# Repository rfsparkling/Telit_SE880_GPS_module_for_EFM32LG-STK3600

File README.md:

This is my evaluation board for interfacing Telit SE880 GPS chip module with EFM32LG-STK3600 EFM32 Leopard Gecko Starter Kit.

I had lot of trouble during the SE880 chip module manufacturing, forget hot air blower! This is a 3D chip module with embedded parts, like capacitors, resistors, etc.
You need to follow the exact heat profile provided by Telit in tha datasheet. So using an SMT heat oven is highly recommended! 

My PCB is assembled (by professional contract manufacturer) and I confirm: it works! The parts are correct.

I have assambled PCBs to sell, please contact me about the details!

Validated Eagle Parts in this project:
Telit SE880
http://www.telit.com/products/product-service-selector/product-service-selector/show/product/jupiter-se880/

EFM32LG-STK3600 interface connector, pinhead connector
https://www.silabs.com/products/mcu/lowpower/Pages/efm32lg-stk3600.aspx

TI TXS0108E 
8-Bit Bidirectional Voltage-Level Shifter For Open-Drain And Push-Pull Application
http://www.ti.com/product/txs0108e

TI LP5907
250mA, Ultra-Low Noise Low-Dropout Regulator
http://www.ti.com/product/LP5907

AVX / Kyocera
TCXO Oscillators 16.369MHz 1.8Volts 2.5mmx2mm Sine Wave
http://www.mouser.co.uk/Search/Refine.aspx?Keyword=581-KT2520F16ACW18T

Abracon 
ABS06-32.768KHZ-T XTAL
http://www.digikey.com/product-detail/en/ABS06-32.768KHZ-T/535-10104-1-ND/2089921

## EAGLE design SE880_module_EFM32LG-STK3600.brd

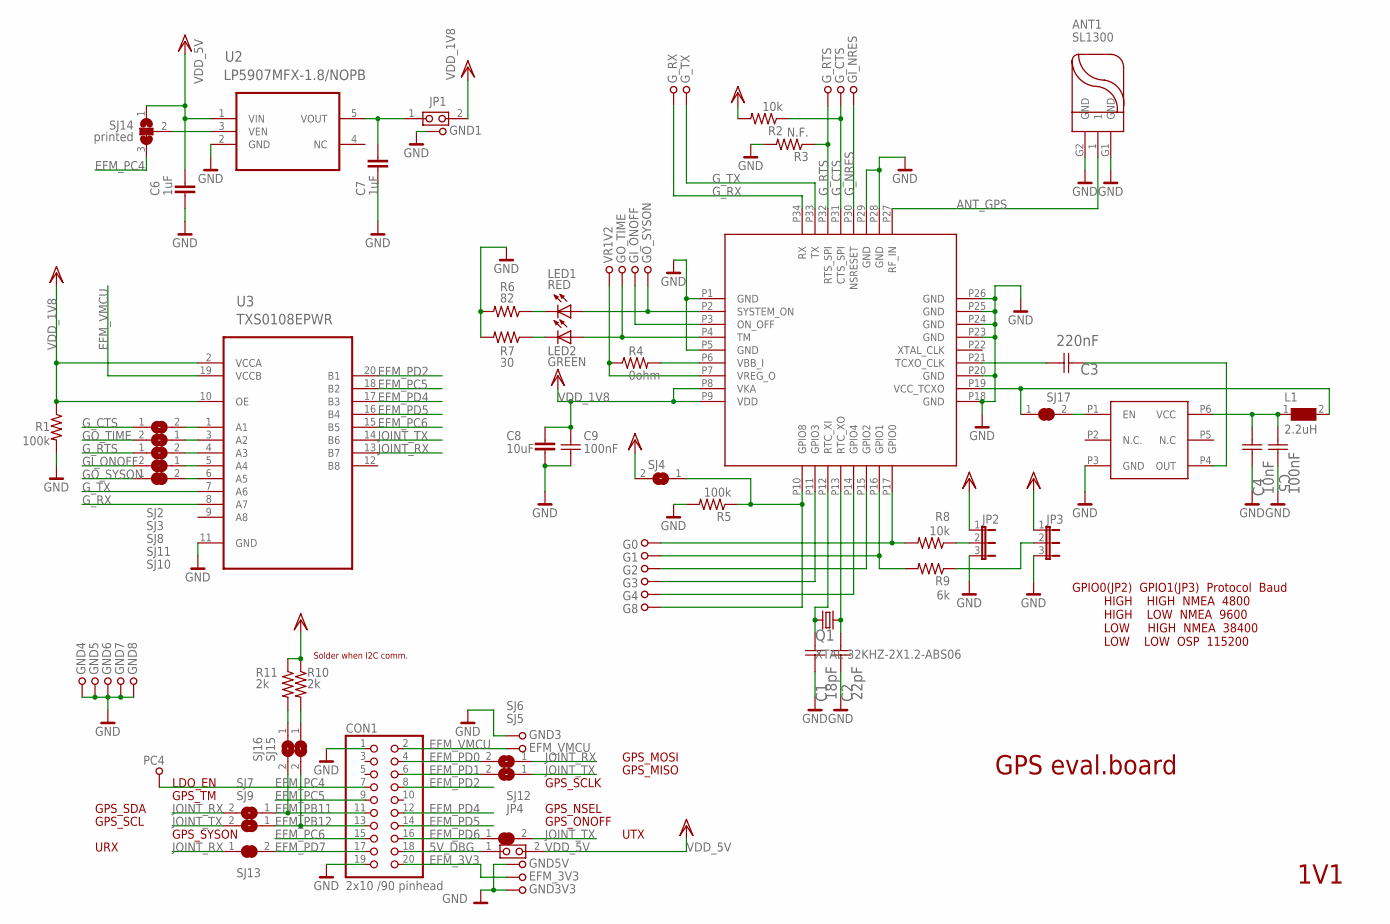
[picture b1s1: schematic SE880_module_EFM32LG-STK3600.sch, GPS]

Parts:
ANT1: SL1300
C1: 18pF; CAPC1005X60N
C2: 22pF; CAPC1005X60N
C3: 220nF; CAPC1005X60N
C4: 10nF; CAPC1005X60N
C5, C9: 100nF; CAPC1005X60N
C6, C7: 1uF; 0603
C8: 10uF; 0603
CON1: 2x10 /90 pinhead; 2X10/90_FEMALE_EFM_MUTANT
EFM_3V3: TESTPOINT39MIL; TESTPOINT1,0
EFM_VMCU: TESTPOINT39MIL; TESTPOINT1,0
G0, G1, G2, G3, G4, G8: TESTPOINT39MIL; TESTPOINT1,0
GI_NRES: TESTPOINT39MIL; TESTPOINT1,0
GI_ONOFF: TESTPOINT39MIL; TESTPOINT1,0
GND1, GND3, GND3V3, GND4, GND5, GND5V, GND6, GND7, GND8: TESTPOINT39MIL; TESTPOINT1,0
GO_SYSON: TESTPOINT39MIL; TESTPOINT1,0
GO_TIME: TESTPOINT39MIL; TESTPOINT1,0
G_CTS: TESTPOINT39MIL; TESTPOINT1,0
G_RTS: TESTPOINT39MIL; TESTPOINT1,0
G_RX: TESTPOINT39MIL; TESTPOINT1,0
G_TX: TESTPOINT39MIL; TESTPOINT1,0
JP1, JP4: JUMPER2-A; PIN2-1R
JP2, JP3: jumper 2mm; JP2
L1: 2.2uH; WE-KI_1008_B
LED1: RED; LED-0603
LED2: GREEN; LED-0603
PC4: TESTPOINT39MIL; TESTPOINT1,0
Q1: XTAL-32KHZ-2X1.2-ABS06; CRYSTAL-SMD-2X1.2-ABS06
Q3: KT2520F16369ACW18TAN; TCXO_2.5X2MM
R1, R5: 100k; R0402
R2, R8: 10k; R0402
R3: N.F.; R0402
R4: 0ohm; 0603-RES
R6: 82; R0402
R7: 30; R0402
R9: 6k; R0402
R10, R11: 2k; R0402
SJ2, SJ3, SJ4, SJ5, SJ6, SJ7, SJ8, SJ9, SJ15, SJ16: printed; JUMPER_SMD_SJ
SJ10, SJ11, SJ12, SJ13, SJ17: printed; JUMPER_SMD_SJ_1
SJ14: printed; JUMPER_SMD_SJ2A
U1: Telit SE880 GPS receiver; LGA-34
U2: LP5907MFX-1.8/NOPB; SOT-23/5-NEW
U3: TXS0108EPWR; SOP65P640X120-20N
VR1V2: TESTPOINT39MIL; TESTPOINT1,0

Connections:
5V_DBG: CON1.18, JP4.1 (A)
ANT_GPS: ANT1.1, U1.P27 (RF_IN)
EFM_3V3: CON1.20, EFM_3V3.1
EFM_PB11: CON1.11, SJ7.1, SJ16.2
EFM_PB12: CON1.13, SJ9.1, SJ15.2
EFM_PC4: CON1.7, PC4.1, SJ14.3
EFM_PC5: CON1.9, U3.18 (B2)
EFM_PC6: CON1.15, U3.15 (B5)
EFM_PD0: CON1.4, SJ6.2
EFM_PD1: CON1.6, SJ5.2
EFM_PD2: CON1.8, U3.20 (B1)
EFM_PD4: CON1.12, U3.17 (B3)
EFM_PD5: CON1.14, U3.16 (B4)
EFM_PD6: CON1.16, SJ12.1
EFM_PD7: CON1.17, SJ13.2
EFM_VMCU: CON1.2, EFM_VMCU.1, U3.19 (VCCB)
GI_ONOFF: GI_ONOFF.1, SJ11.2, U1.P3 (ON_OFF)
GND: ANT1.G1 (GND), ANT1.G2 (GND), C1.2 (C2), C2.2 (C2), C4.2 (C2), C5.2 (C2), C6.1, C7.1, C8.1, C9.2 (C2), CON1.1, CON1.19, GND1.1, GND3.1, GND3V3.1, GND4.1, GND5.1, GND5V.1, GND6.1, GND7.1, GND8.1, JP2.3, JP3.3, Q3.P3 (GND), R1.2, R3.2, R5.2, R6.2, R7.2, U1.P1 (GND), U1.P5 (GND), U1.P18 (GND), U1.P20 (GND), U1.P23 (GND), U1.P24 (GND), U1.P25 (GND), U1.P26 (GND), U1.P28 (GND), U1.P29 (GND), U2.2 (GND), U3.11 (GND)
GO_SYSON: GO_SYSON.1, LED1.A, SJ10.1, U1.P2 (SYSTEM_ON)
GO_TIME: GO_TIME.1, LED2.A, SJ3.2, U1.P4 (TM)
G_CTS: G_CTS.1, R2.1, SJ2.1, U1.P31 (CTS_SPI)
G_NRES: GI_NRES.1, U1.P30 (NSRESET)
G_RTS: G_RTS.1, R3.1, SJ8.1, U1.P32 (RTS_SPI)
G_RX: G_RX.1, U1.P34 (RX), U3.8 (A7)
G_TX: G_TX.1, U1.P33 (TX), U3.7 (A6)
JOINT_RX: SJ6.1, SJ7.2, SJ13.1, U3.13 (B7)
JOINT_TX: SJ5.1, SJ9.2, SJ12.2, U3.14 (B6)
unnamed: C2.1 (C1), Q1.P$2 (2), U1.P13 (RTC_XO)
unnamed: C1.1 (C1), Q1.P$1 (1), U1.P12 (RTC_XI)
unnamed: C3.1 (C1), U1.P21 (TCXO_CLK)
unnamed: C3.2 (C2), Q3.P4 (OUT)
unnamed: C4.1 (C1), C5.1 (C1), L1.1, Q3.P6 (VCC)
unnamed: L1.2, SJ17.1, U1.P19 (VCC_TCXO)
unnamed: G3.1, U1.P11 (GPIO3)
unnamed: C7.2, JP1.1 (A), U2.5 (VOUT)
unnamed: G4.1, U1.P14 (GPIO4)
unnamed: G2.1, U1.P15 (GPIO2)
unnamed: G1.1, R9.2, U1.P16 (GPIO1)
unnamed: G0.1, R8.2, U1.P17 (GPIO0)
unnamed: SJ14.2, U2.3 (VEN)
unnamed: Q3.P1 (EN), SJ17.2
unnamed: R10.2, SJ15.1
unnamed: LED1.C, R6.1
unnamed: R11.2, SJ16.1
unnamed: SJ2.2, U3.1 (A1)
unnamed: R4.2, U1.P6 (VBB_I)
unnamed: R4.1, U1.P7 (VREG_O), VR1V2.1
unnamed: G8.1, R5.1, SJ4.1, U1.P10 (GPIO8)
unnamed: LED2.C, R7.1
unnamed: JP2.2, R8.1
unnamed: JP3.2, R9.1
unnamed: SJ3.1, U3.3 (A2)
unnamed: SJ8.2, U3.4 (A3)
unnamed: SJ11.1, U3.5 (A4)
unnamed: SJ10.2, U3.6 (A5)
VDD_1V8: C8.2, C9.1 (C1), JP1.2 (B), JP2.1, JP3.1, R1.1, R2.2, R10.1, R11.1, SJ4.2, U1.P8 (VKA), U1.P9 (VDD), U3.2 (VCCA), U3.10 (OE)
VDD_5V: C6.2, JP4.2 (B), SJ14.1, U2.1 (VIN)

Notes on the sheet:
GPS eval.board
1V1
GPIO0(JP2) GPIO1(JP3) Protocol Baud HIGH HIGH NMEA 4800 HIGH LOW NMEA 9600 LOW HIGH NMEA 38400 LOW LOW OSP 115200
Solder when I2C comm.
GPS_NSEL
GPS_ONOFF
GPS_SCLK
GPS_SYSON
GPS_SCL
GPS_SDA
GPS_TM
LDO_EN
UTX
URX
GPS_MOSI
GPS_MISO

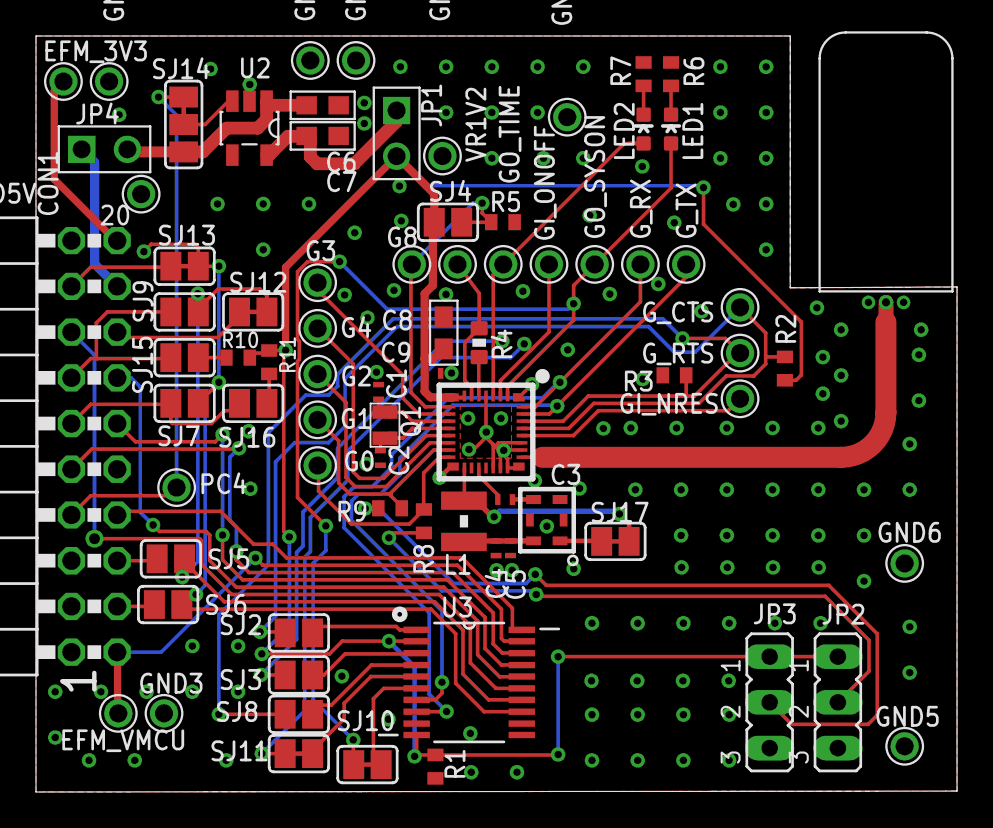
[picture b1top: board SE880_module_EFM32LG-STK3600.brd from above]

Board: 2 copper layers, 51.2 x 42.0 mm, 77 parts (0 on the bottom side), 57 nets.

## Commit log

2015-12-16 :boom::camel: Added .gitattributes & .gitignore files
2015-12-16 adding files
2015-12-16 correction
2015-12-16 adding lic file

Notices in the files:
parts and their libraries:
Wuerth_Elektronik: Copyright: Würth Elektronik eiSos
